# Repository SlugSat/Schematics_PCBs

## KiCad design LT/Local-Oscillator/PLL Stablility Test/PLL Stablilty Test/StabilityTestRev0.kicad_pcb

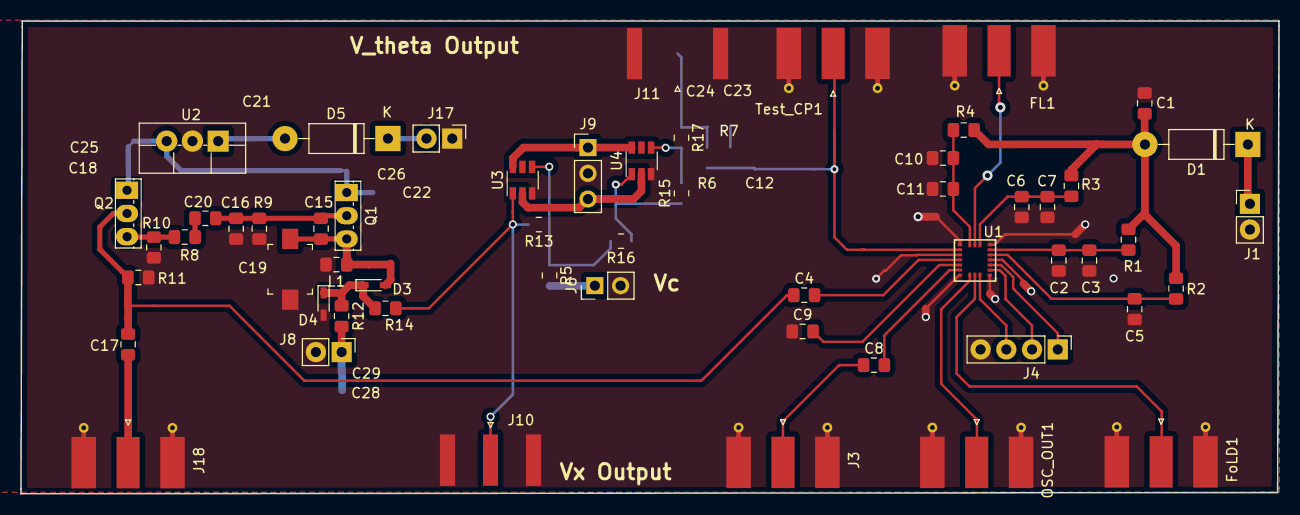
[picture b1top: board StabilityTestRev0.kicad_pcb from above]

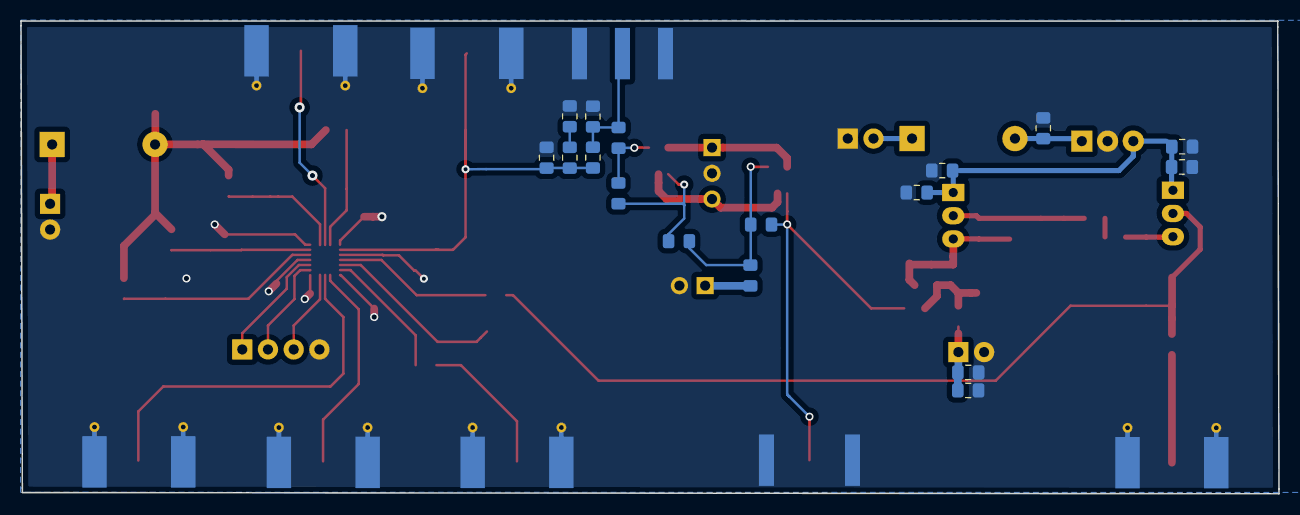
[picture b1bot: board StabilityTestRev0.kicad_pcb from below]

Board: 2 copper layers, 124.2 x 46.7 mm, 68 parts (12 on the bottom side), 38 nets.

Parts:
C1: C; C_0805_2012Metric_Pad1.15x1.40mm_HandSolder
C2, C5, C6, C9, C10, C17, C18, C21, C22, C29: 100nF; C_0805_2012Metric_Pad1.15x1.40mm_HandSolder
C3, C7, C11, C25, C26, C28: 100pF; C_0805_2012Metric_Pad1.15x1.40mm_HandSolder
C4, C8: 1000pF; C_0805_2012Metric_Pad1.15x1.40mm_HandSolder
C12: 12nF; C_0805_2012Metric_Pad1.15x1.40mm_HandSolder
C15: 22pF; C_0805_2012Metric_Pad1.15x1.40mm_HandSolder
C16: 47pF; C_0805_2012Metric_Pad1.15x1.40mm_HandSolder
C19: SGC35060; C_Trimmer_Murata_TZB4-B
C20: 10pF; C_0805_2012Metric_Pad1.15x1.40mm_HandSolder
C23: 80nF; C_0805_2012Metric_Pad1.15x1.40mm_HandSolder
C24: 220nF; C_0805_2012Metric_Pad1.15x1.40mm_HandSolder
D1, D5: DIODE; D_DO-41_SOD81_P10.16mm_Horizontal
D3, D4: 1SV232; D_SC-80_HandSoldering
FL1: Conn_Coaxial; SMA_Molex_73251-1153_EdgeMount_Horizontal
FoLD1: Conn_Coaxial; SMA_Molex_73251-1153_EdgeMount_Horizontal
J1, J6, J8, J17: Conn_01x02_Male; PinHeader_1x02_P2.54mm_Vertical
J3, J18: Conn_Coaxial; SMA_Molex_73251-1153_EdgeMount_Horizontal
J4: Conn_01x04_Male; PinHeader_1x04_P2.54mm_Vertical
J9: Conn_01x03_Male; PinHeader_1x03_P2.54mm_Vertical
J10, J11: Conn_Coaxial; SMA_Amphenol_132289_EdgeMount
L1: 680nH; L_0805_2012Metric_Pad1.15x1.40mm_HandSolder
OSC_OUT1: Conn_Coaxial; SMA_Molex_73251-1153_EdgeMount_Horizontal
Q1, Q2: 2N5486 JFET; TO-251-3_Vertical
R1, R3, R4: 18; R_0805_2012Metric_Pad1.15x1.40mm_HandSolder
R2: 10k; R_0805_2012Metric_Pad1.15x1.40mm_HandSolder
R5, R6, R9, R11, R12, R13, R15, R16, R17: 1k; R_0805_2012Metric_Pad1.15x1.40mm_HandSolder
R7: 62k; R_0805_2012Metric_Pad1.15x1.40mm_HandSolder
R8: 1 Ohm; R_0805_2012Metric_Pad1.15x1.40mm_HandSolder
R10: 100k; R_0805_2012Metric_Pad1.15x1.40mm_HandSolder
R14: 0; R_0805_2012Metric_Pad1.15x1.40mm_HandSolder
Test_CP1: Conn_Coaxial; SMA_Molex_73251-1153_EdgeMount_Horizontal
U1: LMX231X
U2: L7808; TO-220F-3_Vertical
U3, U4: LMH6611; TSOT-23-6

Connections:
8V: C18.2, C22.2, C25.2, C26.2, Q1.1, Q2.1, U2.3
+5V: J9.1, U3.6, U4.6
-5V: J9.3, U3.2, U4.2
CE: C5.2, R2.2, U1.15
CPo: C12.2, R6.2, R7.2, Test_CP1.1, U1.2
Clock: J4.3, U1.10
Data: J4.2, U1.12
FL: FL1.1, U1.19
F_IN: C4.2, U1.4
FoLD: FoLD1.1, U1.9
GND: C1.1, C2.1, C3.1, C5.1, C6.1, C7.1, C9.1, C10.1, C11.1, C12.1, C16.1, C18.1, C19.2, C21.2, C22.1, C23.2, C24.2, C25.1, C26.1, C28.1, C29.1, D4.2, FL1.2, FoLD1.2, J1.2, J3.2, J4.4, J6.2, J8.2, J9.2, J10.2, J11.2, J17.1, J18.2, L1.2, OSC_OUT1.2, R9.2, R10.2, R11.2, Test_CP1.2, U1.1, U1.3, U1.7, U1.11, U1.14, U1.17, U2.2, U3.3, U4.3
LE: J4.1, U1.13
unnamed: C8.1, J3.1
unnamed: C9.2, U1.5
unnamed: C15.1, C16.2, C20.1, Q1.2, R9.1
unnamed: C15.2, C19.1, D3.2, L1.1, Q1.3
unnamed: C4.1, C17.1, Q2.2, R11.1
unnamed: C17.2, J18.1
unnamed: C20.2, R8.2
unnamed: C21.1, D5.2, U2.1
unnamed: C23.1, R7.1
unnamed: C24.1, J11.1, R6.1, R17.1
unnamed: C28.2, C29.2, J8.1, R12.2
unnamed: D1.1, J1.1
unnamed: D3.1, D4.1, R12.1, R14.2
unnamed: D5.1, J17.2
unnamed: J6.1, R5.2
unnamed: J10.1, R13.2, R14.1, U3.1
unnamed: Q2.3, R8.1, R10.1
unnamed: R5.1, R13.1, R16.2, U3.4
unnamed: R15.1, R16.1, U4.1
unnamed: R15.2, R17.2, U4.4
OSC_IN: C8.2, U1.6
OSC_OUT: OSC_OUT1.1, U1.8
PLL_Power: C1.2, D1.2, R1.1, R2.1, R3.1, R4.1
V_uC: C2.2, C3.2, R1.2, U1.16
Vcc: C6.2, C7.2, R3.2, U1.18
Vp: C10.2, C11.2, R4.2, U1.20
